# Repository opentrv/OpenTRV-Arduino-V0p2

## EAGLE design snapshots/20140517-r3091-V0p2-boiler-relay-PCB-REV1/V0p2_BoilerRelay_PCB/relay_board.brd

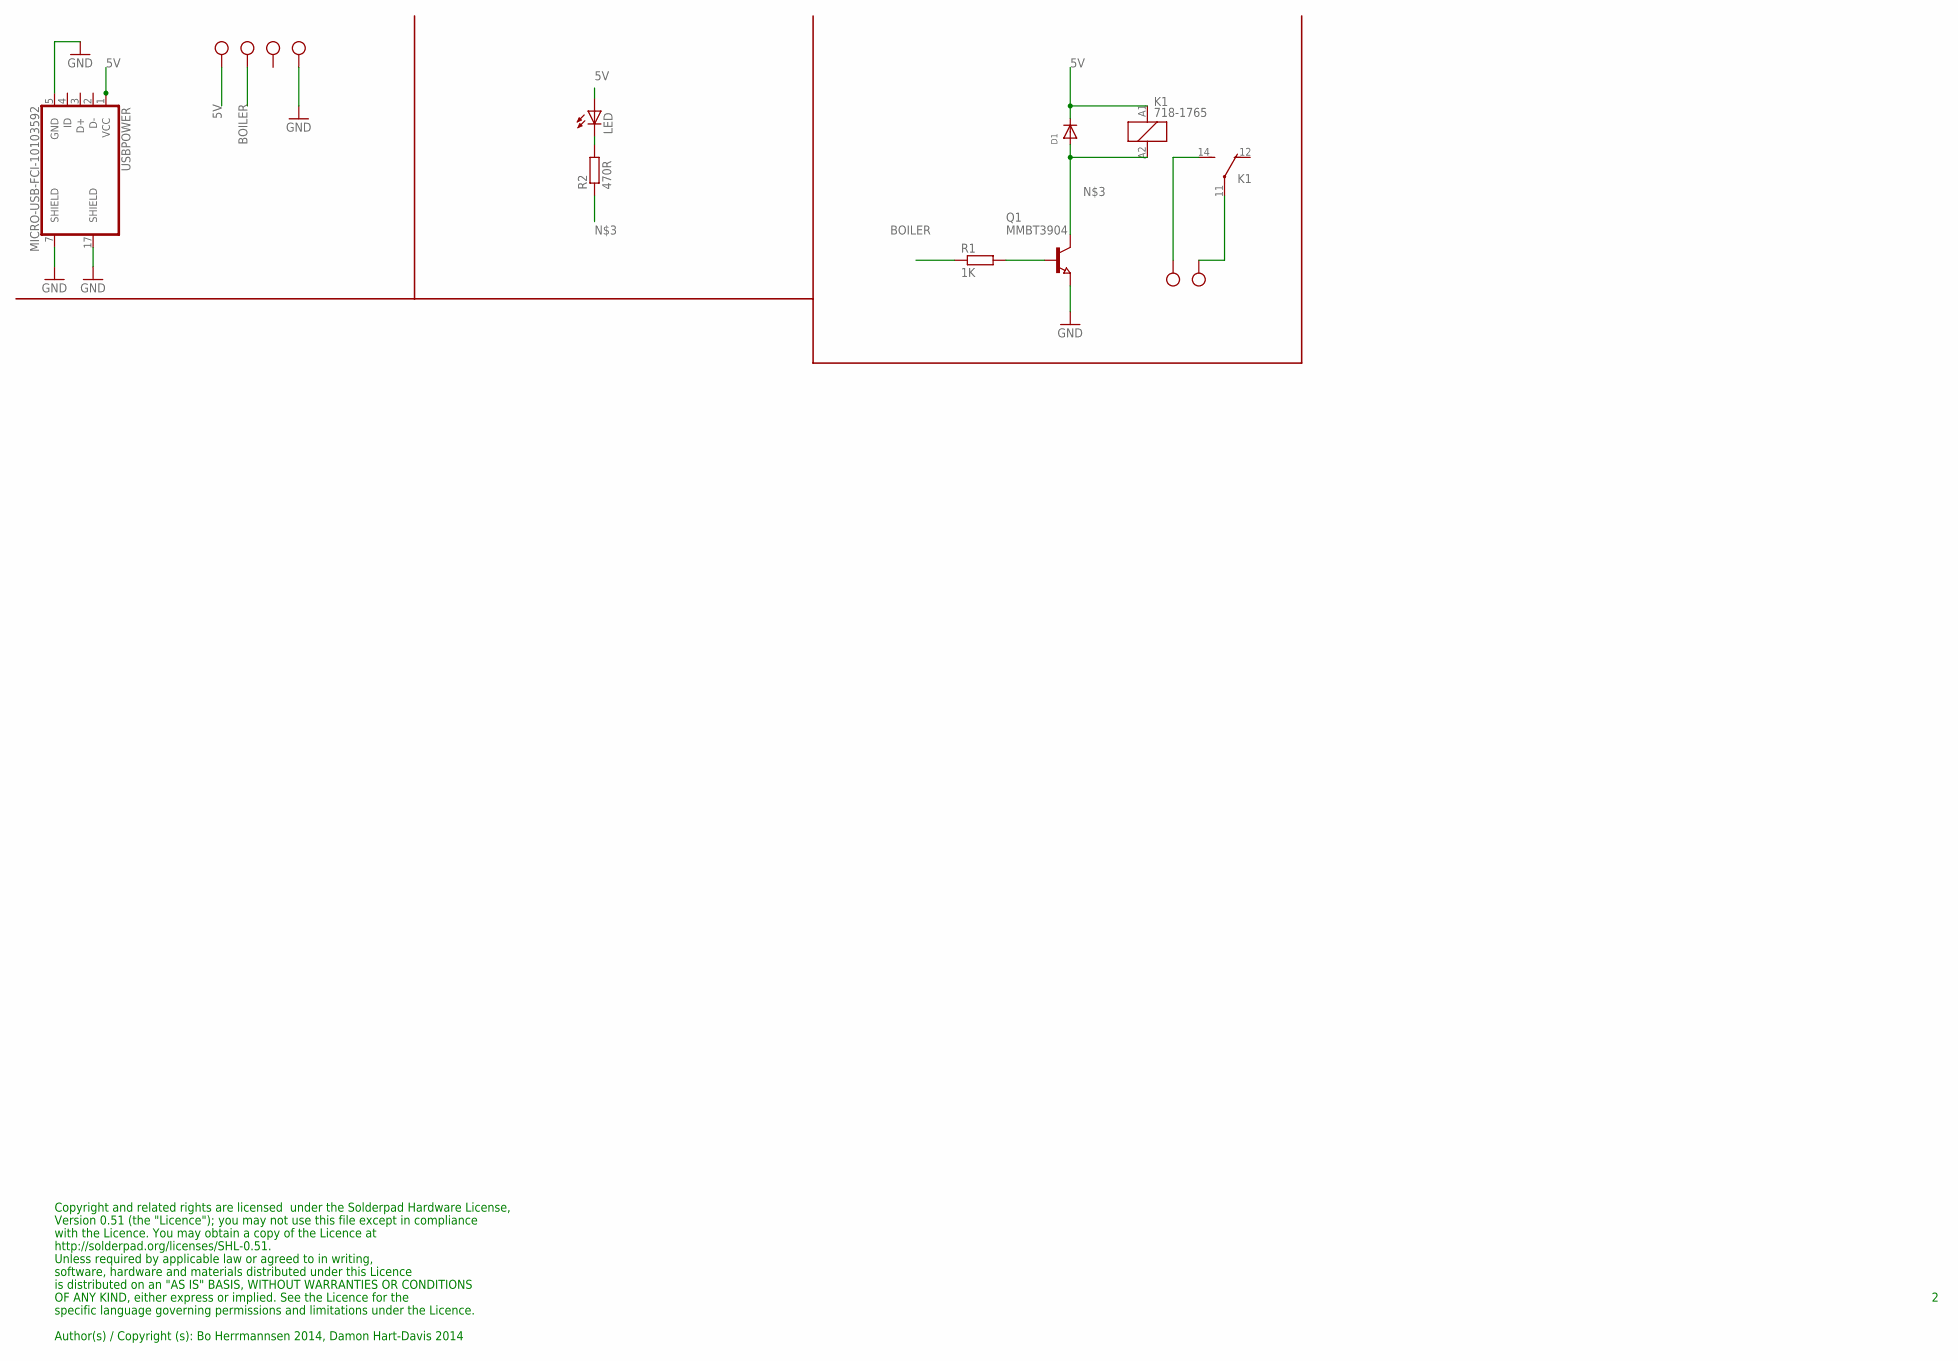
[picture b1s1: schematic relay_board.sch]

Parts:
D1: DIODESMA; SMADIODE
K1: 718-1765
LED: LED3MM
Q1: MMBT3904; SOT23
R1: 1K; R0603
R2: 470R; R0603
USBPOWER: MICRO-USB-FCI-10103592
X1, X2, X3: W237-102; SCREWTERMINAL

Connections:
5V: D1.C, K1.A1 (1), LED.A, USBPOWER.1 (VCC), X1.2
BOILER: R1.1, X1.1
GND: Q1.2 (E), USBPOWER.5 (GND), USBPOWER.7 (SHIELD), USBPOWER.17 (SHIELD), X2.2
unnamed: K1.14 (S), X3.1
unnamed: D1.A, K1.A2 (2), Q1.3 (C), R2.1
unnamed: K1.11, X3.2
unnamed: Q1.1 (B), R1.2
unnamed: LED.K (C), R2.2

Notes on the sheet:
Copyright and related rights are licensed under the Solderpad Hardware License,
Version 0.51 (the "Licence"); you may not use this file except in compliance
with the Licence. You may obtain a copy of the Licence at
http://solderpad.org/licenses/SHL-0.51.
Unless required by applicable law or agreed to in writing,
software, hardware and materials distributed under this Licence
is distributed on an "AS IS" BASIS, WITHOUT WARRANTIES OR CONDITIONS
Author(s) / Copyright (s): Bo Herrmannsen 2014, Damon Hart-Davis 2014
OF ANY KIND, either express or implied. See the Licence for the
specific language governing permissions and limitations under the Licence.

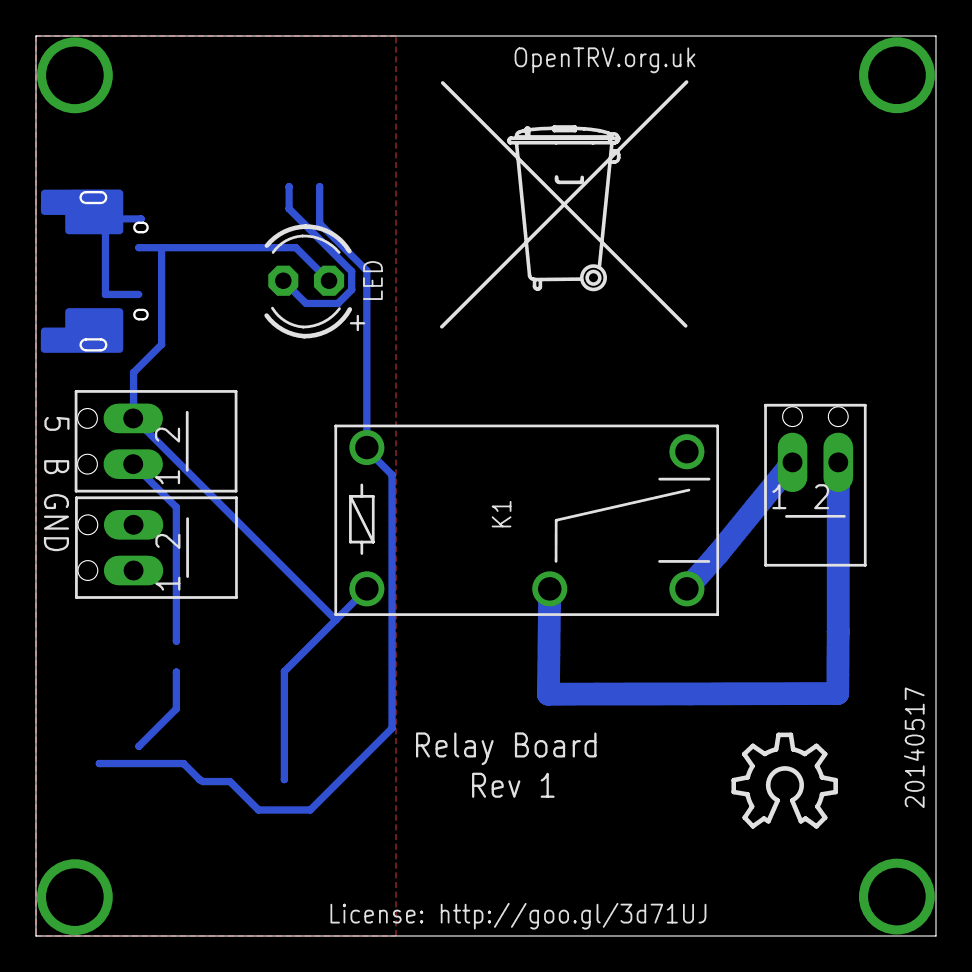
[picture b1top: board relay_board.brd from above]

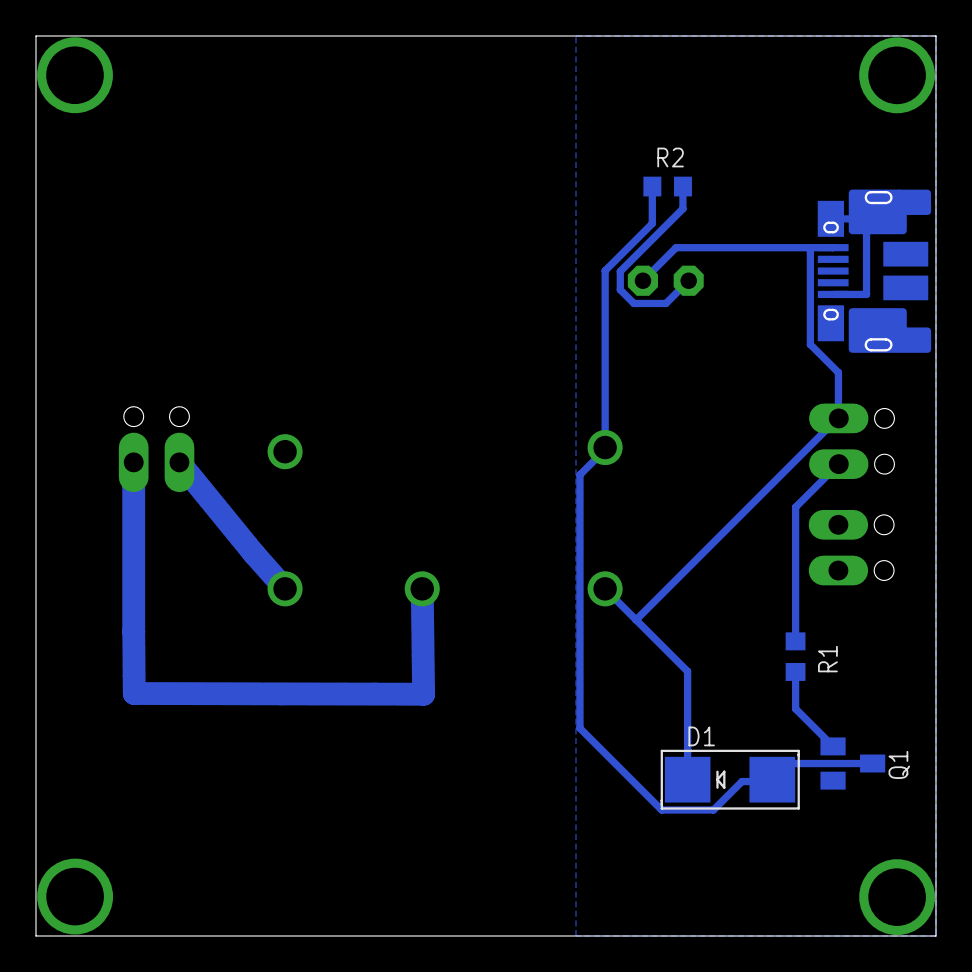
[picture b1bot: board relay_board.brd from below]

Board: 2 copper layers, 50.0 x 50.0 mm, 12 parts (5 on the bottom side), 8 nets.

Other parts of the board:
U$1: OSHW_10X200_NOTEXT
U$2: TONNE

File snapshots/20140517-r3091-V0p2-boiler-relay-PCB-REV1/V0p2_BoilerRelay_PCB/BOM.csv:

# of boards ttl,,,,5,PURPLE MEANS OK,,,
,,,,,,,,
,,,,,,,,
Quantity per board,Need to order,Seller Stock No,Manufacturer,Manufacturer Part. No.,Description,Legend,Supplier,Direct Link
1,5,714-2334,FCI,10103592-0001LF,Micro USB socket,USBPOWER,RS Components,http://uk.rs-online.com/web/p/micro-usb-connectors/7142334/
2,10, 220-4260,Phoenix Contact,MPT 0.5/ 2-2.54,Screw Terminal 2-way,"X1, X2",RS Components,http://uk.rs-online.com/web/p/pcb-terminal-blocks/2204260
1,5,710-0104,TE Connectivity,282834-2,Screw Terminal 2-way,X3,RS Components,http://uk.rs-online.com/web/p/pcb-terminal-blocks/7100104/
1,5,826-515,Avago Technologies,HLMP-K150,LED RED,LED,RS Components,http://uk.rs-online.com/web/p/visible-leds/0826515
1,5,213-2222,TE Connectivity,CRG0603F470R,470ohm,R2,RS Components,http://uk.rs-online.com/web/p/surface-mount-fixed-resistors/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
1,5,739-0303,Fairchild Semiconductor,MMBT3904,Transistor NPN,Q1,RS Components,http://uk.rs-online.com/web/p/bipolar-transistors/7390303/
1,5,721-7340,Panasonic,ERJP03F1001V,1Kohm,R1,RS Components,http://uk.rs-online.com/web/p/surface-mount-fixed-resistors/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
1,5,796-9344,Taiwan Semiconductor,RS1D,Blocking Diode,D1,RS Components,http://uk.rs-online.com/web/p/rectifier-schottky-diodes/7969344/
1,5,680-3595,TE Connectivity,PE014005,5V Non latch relay,K1,RS Components,http://uk.rs-online.com/web/p/non-latching-relays/6803593/
,,,,,,,,
1,5,,,,5*5cm Prototype Board,,Itead Studio,

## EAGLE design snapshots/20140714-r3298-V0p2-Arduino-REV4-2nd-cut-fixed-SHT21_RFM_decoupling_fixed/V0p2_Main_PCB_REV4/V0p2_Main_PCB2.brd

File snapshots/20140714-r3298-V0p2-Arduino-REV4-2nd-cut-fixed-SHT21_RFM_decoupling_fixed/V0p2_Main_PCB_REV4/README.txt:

REV 4 is RFM23B and phototransistor and SHT21 temp_RH sensor.

Using ATmega pinout for Eagle from:
http://www.faludi.com/2008/10/07/arduino-avr-library-for-eagle-layout-editor/
without explicit licence but following email permission:

    From: Rob Faludi
    Date: 13 May 2013 00:34:52 GMT+01:00
    Subject: Re: A comment from Damon Hart-Davis

    Sure, go for it!

    A new submission (form: "Contact Form")
    ============================================
    Submitted on: May 12, 2013
    Via: /contact/

    --------------------------Contact Me----------------------

    Your Name:                      Damon Hart-Davis

    Message:
    May we use your Eagle ATmega package/library:

    http://www.faludi.com/2008/10/07/arduino-avr-library-for-eagle-layout-editor/

    In our Apache/Solderpad-licenced OpenTRV project please?

    Rgds

    Damon
    http://opentrv.org.uk/

Note ITEADstudio .dru and .cam files downloaded from their site AND NOT COVERED BY OUR APACHE LICENCE
though ITEADstudio would probably be happy for you to use their service like we did!

Component-ordering document: https://docs.google.com/spreadsheet/ccc?key=0Aptz2VDSxR-zdFl5eGpmRi10SF95YnpsSWdwdnZKSFE#gid=0

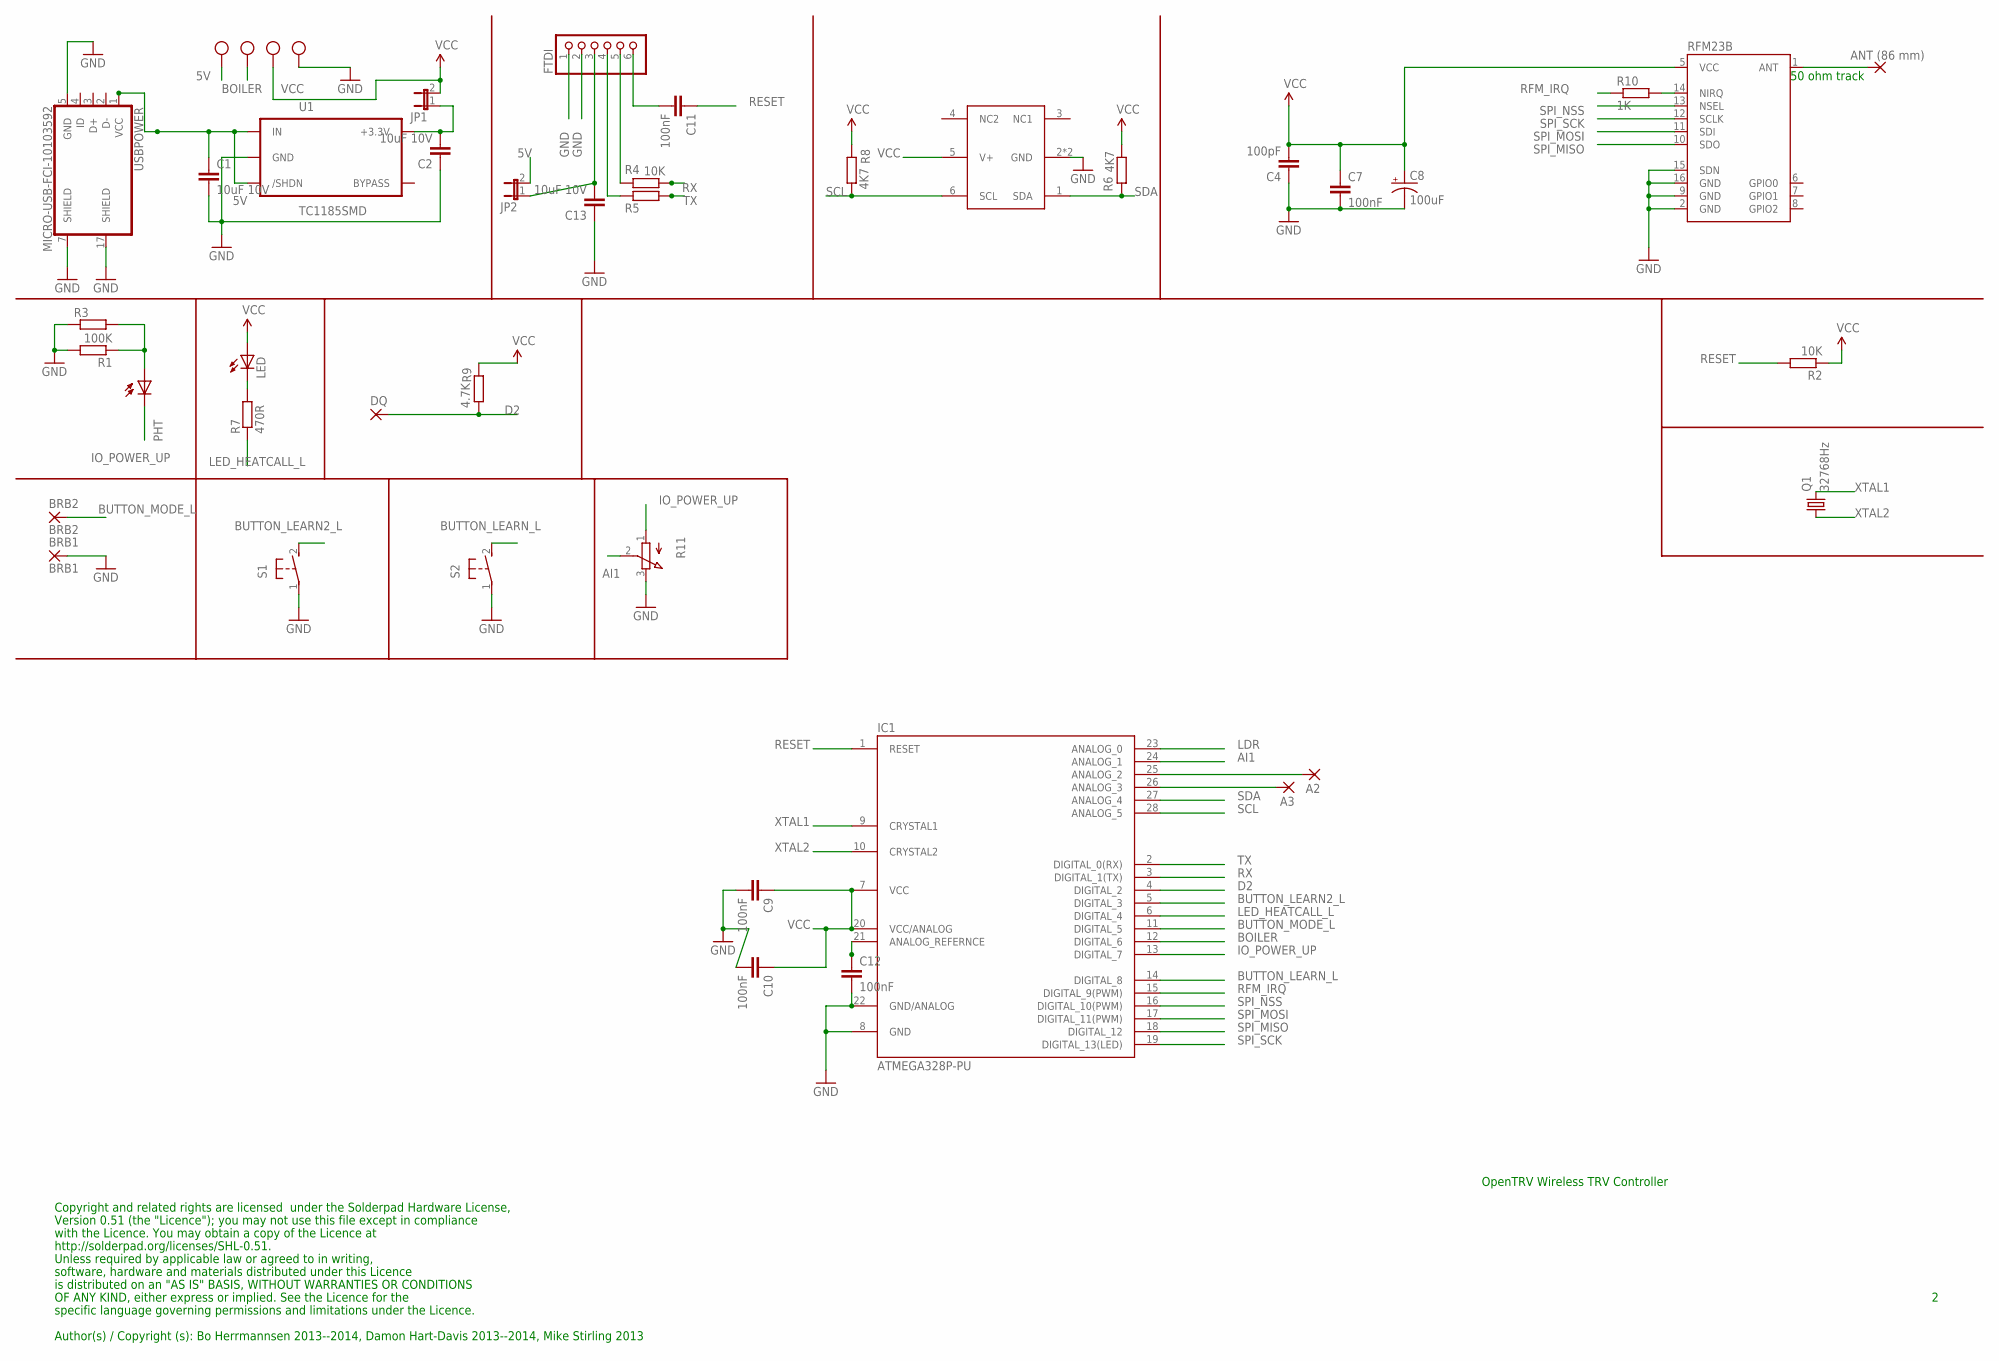
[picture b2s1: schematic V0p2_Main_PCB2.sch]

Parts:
A2, A3: 2,15/1,0
ANT1: ANT (86 mm); 2,15/1,0
BRB1: BRB1; 2,15/1,0
BRB2: BRB2; 2,15/1,0
C1, C2, C13: 10uF 10V; C0603
C4: 100pF; C0603
C7, C9, C10, C11, C12: 100nF; C0603
C8: 100uF; EIA3216
DQ: 2,15/1,0
FTDI: PINHD-1X6/90; 1X06/90
IC1: ATMEGA328P-PU; DIL28-3
JP1, JP2: JP1E; JP1
LED: LED3MM
PHT: BPX65
Q1: 32768Hz; MC-306
R1: 100K; R0603
R2, R4, R5: 10K; R0603
R3: R-EU_0309/V; 0309V
R6, R8: 4K7; R0603
R7: 470R; R0603
R9: 4.7K; R0603
R10: 1K; R0603
R11: EVUE2A; EVUE
RFM23B: RFM23B; RFM23-XXX-S1
S1, S2: 31-XX; B3F-31XX
U1: TC1185SMD; TC1185
U$4: SHT21
USBPOWER: MICRO-USB-FCI-10103592
X1, X2: W237-102; SCREWTERMINAL

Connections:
5V: C1.1, JP2.2, U1.1 (IN), U1.3 (/SHDN), USBPOWER.1 (VCC), X1.2
AI1: IC1.24 (ANALOG_1), R11.2 (S)
BOILER: IC1.12 (DIGITAL_6), X1.1
BUTTON_LEARN2_L: IC1.5 (DIGITAL_3), S1.2 (S)
BUTTON_LEARN_L: IC1.14 (DIGITAL_8), S2.2 (S)
BUTTON_MODE_L: BRB2.1, IC1.11 (DIGITAL_5)
D2: DQ.1, IC1.4 (DIGITAL_2), R9.1
GND: BRB1.1, C1.2, C2.1, C4.1, C7.2, C8.C (-), C9.2, C10.2, C12.2, C13.1, FTDI.1, FTDI.2, IC1.8 (GND), IC1.22 (GND/ANALOG), R1.2, R3.1, R11.3 (E), RFM23B.2 (GND), RFM23B.9 (GND), RFM23B.15 (SDN), RFM23B.16 (GND), S1.1, S2.1, U1.2 (GND), U$4.2 (GND), U$4.P$1 (GND), USBPOWER.5 (GND), USBPOWER.7 (SHIELD), USBPOWER.17 (SHIELD), X2.2
IO_POWER_UP: IC1.13 (DIGITAL_7), PHT.K (C), R11.1 (A)
LDR: IC1.23 (ANALOG_0), PHT.A, R1.1, R3.2
LED_HEATCALL_L: IC1.6 (DIGITAL_4), R7.1
unnamed: C11.2, FTDI.6
unnamed: FTDI.4, R5.2
unnamed: FTDI.5, R4.2
unnamed: C12.1, IC1.21 (ANALOG_REFERNCE)
unnamed: R10.2, RFM23B.14 (NIRQ)
unnamed: C2.2, JP1.1, U1.5 (+3.3V)
unnamed: C13.2, FTDI.3, JP2.1
unnamed: LED.K (C), R7.2
unnamed: A2.1, IC1.25 (ANALOG_2)
unnamed: A3.1, IC1.26 (ANALOG_3)
unnamed: ANT1.1, RFM23B.1 (ANT)
RESET: C11.1, IC1.1 (RESET), R2.2
RFM_IRQ: IC1.15 (DIGITAL_9(PWM)), R10.1
RX: IC1.3 (DIGITAL_1(TX)), R4.1
SCL: IC1.28 (ANALOG_5), R8.1, U$4.6 (SCL)
SDA: IC1.27 (ANALOG_4), R6.2, U$4.1 (SDA)
SPI_MISO: IC1.18 (DIGITAL_12), RFM23B.10 (SDO)
SPI_MOSI: IC1.17 (DIGITAL_11(PWM)), RFM23B.11 (SDI)
SPI_NSS: IC1.16 (DIGITAL_10(PWM)), RFM23B.13 (NSEL)
SPI_SCK: IC1.19 (DIGITAL_13(LED)), RFM23B.12 (SCLK)
TX: IC1.2 (DIGITAL_0(RX)), R5.1
VCC: C4.2, C7.1, C8.A (+), C9.1, C10.1, IC1.7 (VCC), IC1.20 (VCC/ANALOG), JP1.2, LED.A, R2.1, R6.1, R8.2, R9.2, RFM23B.5 (VCC), U$4.5 (V+), X2.1
XTAL1: IC1.9 (CRYSTAL1), Q1.4 (2)
XTAL2: IC1.10 (CRYSTAL2), Q1.1

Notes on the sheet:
Copyright and related rights are licensed under the Solderpad Hardware License,
Version 0.51 (the "Licence"); you may not use this file except in compliance
with the Licence. You may obtain a copy of the Licence at
http://solderpad.org/licenses/SHL-0.51.
Unless required by applicable law or agreed to in writing,
software, hardware and materials distributed under this Licence
is distributed on an "AS IS" BASIS, WITHOUT WARRANTIES OR CONDITIONS
Author(s) / Copyright (s): Bo Herrmannsen 2013--2014, Damon Hart-Davis 2013--2014, Mike Stirling 2013
OpenTRV Wireless TRV Controller
OF ANY KIND, either express or implied. See the Licence for the
specific language governing permissions and limitations under the Licence.
50 ohm track

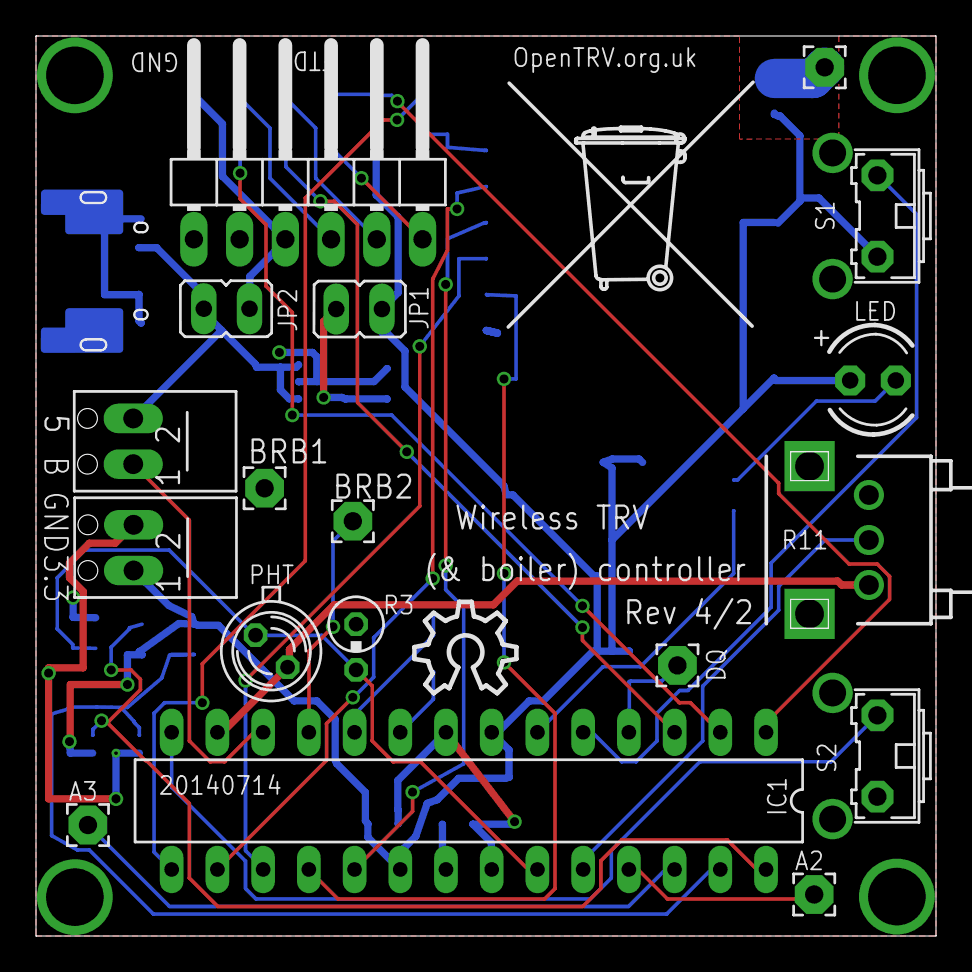
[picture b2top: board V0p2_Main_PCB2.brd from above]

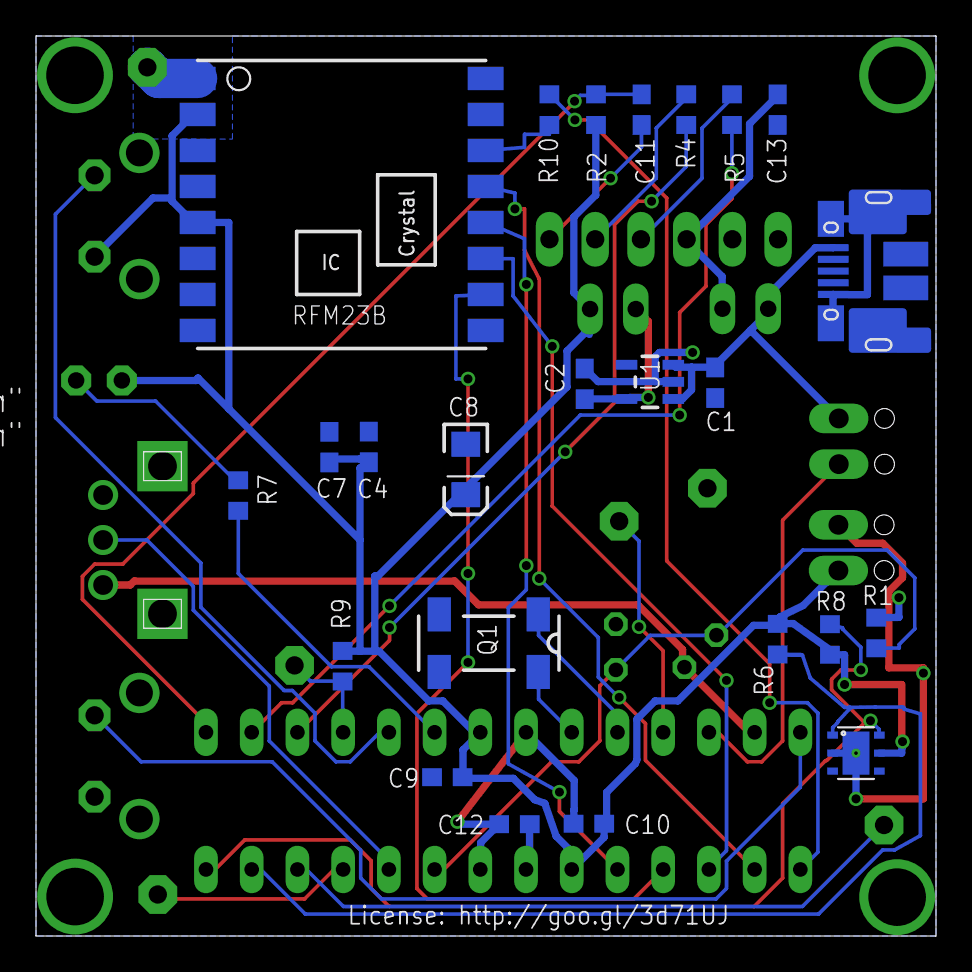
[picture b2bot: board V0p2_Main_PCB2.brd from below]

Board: 2 copper layers, 50.0 x 50.0 mm, 44 parts (24 on the bottom side), 35 nets.

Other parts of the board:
U$1: OSHW_10X200_NOTEXT
U$2: TONNE

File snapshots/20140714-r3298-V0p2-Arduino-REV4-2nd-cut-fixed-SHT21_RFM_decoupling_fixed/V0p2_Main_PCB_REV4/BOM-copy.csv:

# of boards ttl,,,,5,Green MEANS OK,,,
,,,,,,,,
,,,,,,,,
Quantity per board,Need to order,Seller Stock No,Manufacturer,Manufacturer Part. No.,Description,Legend,Supplier,Direct Link
1,5,714-2334,FCI,10103592-0001LF,Micro USB socket,USBPOWER,RS Components,http://uk.rs-online.com/web/p/micro-usb-connectors/7142334/
1,5,628-3661,Microchip,TC1185-3.3VCT713,3.3V Regulator,U1,RS Components,http://uk.rs-online.com/web/p/low-dropout-voltage-regulators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
3,15,741-4434,TDK,C1608X5R0J106M080AB,10 uF,"C1, C2, C13",RS Components,http://uk.rs-online.com/web/p/ceramic-multilayer-capacitors/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
1,5, 213-2581,TE Connectivity,CRG0603F220K,220Kohm,R1,RS Components,http://uk.rs-online.com/web/p/surface-mount-fixed-resistors/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
3,15,213-2418,TE Connectivity,CRG0603F10K,10 Kohm,"R2, R4, R5",RS Components,http://uk.rs-online.com/web/p/surface-mount-fixed-resistors/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
3,15,213-2367,TE Connectivity,CRG0603F4K7,4.7Kohm,"R6, R8, R9",RS Components,http://uk.rs-online.com/web/p/surface-mount-fixed-resistors/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
1,5,213-2222,TE Connectivity,CRG0603F470R,470ohm,R7,RS Components,http://uk.rs-online.com/web/p/surface-mount-fixed-resistors/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
5,25,264-4630,Kemet,C0603C104K4RAC,100nF,"C7, C9, C10, C11, C12",RS Components,http://uk.rs-online.com/web/p/ceramic-multilayer-capacitors/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
1,5,464-6391,AVX,06035A101JAT2A,100pF,C4,RS Components,http://uk.rs-online.com/web/p/ceramic-multilayer-capacitors/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
1,5,749-2059,Murata,GRM31CR60G107ME39L,100uF,C8,RS Components,http://uk.rs-online.com/web/p/ceramic-multilayer-capacitors/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
1,5,667-6120,EPSON TOYOCOM,"MC-306, 32.768kHz, 20ppm, 6pF",Crystal,Q1,RS Components,http://uk.rs-online.com/web/p/crystal-units/6676120
2,10, 220-4260,Phoenix Contact,MPT 0.5/ 2-2.54,Screw Terminal 2-way,"X1, X2",RS Components,http://uk.rs-online.com/web/p/pcb-terminal-blocks/2204260
1,5,786-5554,Sensirion,SHT21,SHT21,SHT21,RS Components,http://uk.rs-online.com/web/p/temperature-humidity-sensors/7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
1,5,681-2537,TE Connectivity,826947-6,FTDI 90 angle header,FTDI,RS Components,http://uk.rs-online.com/web/p/pcb-headers/6812537
1,5,674-2450,ASSMANN WSW,A 28-LC/7-T,28 pin IC Socket,IC1,RS Components,http://uk.rs-online.com/web/p/dil-sockets/6742450
2,10,251-8086,RS,W81102T3825RC,Jumper pin,"JP1, JP2",RS Components,http://uk.rs-online.com/web/p/pcb-headers/2518086
2,10,680-1461,TE Connectivity,1-881545-1,Jumper cap,"[fit to JP1, JP2]",RS Components,http://uk.rs-online.com/web/p/jumpers-shunts/6801461
1,5,826-515,Avago Technologies,HLMP-K150,LED RED,LED,RS Components,http://uk.rs-online.com/web/p/visible-leds/0826515
1,5,700-0776,Vishay,TEPT4400,60° Visible Light Phototransistor,PHT,RS Components,http://uk.rs-online.com/web/p/phototransistors/7000776/
2,10,758-1991,Alps,SKHHLQA010,Learn,"S1, S2",RS Components,http://uk.rs-online.com/web/p/tactile-switches/7581991
1,5,263-3006,Alps,RK09K1110A96,Pot. Meter,R11,RS Components,http://uk.rs-online.com/web/p/potentiometers/2633006
1,5,213-2266,TE Connectivity,CRG0603F1K0,1Kohm,R10,RS Components,http://uk.rs-online.com/web/p/surface-mount-fixed-resistors/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
1,5,119-2958,Apem,1415NC RED,Mode button,Mode,RS Components,http://uk.rs-online.com/web/p/push-button-switches/1192958
1,5,712-5320,,,84mm* of insulated semi-flexible antenna wire (~0.33sqmm). *Depends on PCB track length.,ANT,,http://uk.rs-online.com/web/p/hookup-equipment-wire/7125320
1,5,696-2260,Atmel,ATMEGA328P-PU,ATmega328P-PU,IC1,RS Components,http://uk.rs-online.com/web/p/microcontrollers/6962260
1,5,RFM23-868-S1,HopeRF,RFM23-868-S1,RFM23B,RFM23,ideetron.nl,http://www.hoperf.nl/RFM23B
1,5,,,,5*5cm Prototype Board,MAIN Board,Itead Studio,
,,,,,,,,
EXPERIMENTATION:,,,,,,,,
0,0,,,,,R3,NOT FITTED,

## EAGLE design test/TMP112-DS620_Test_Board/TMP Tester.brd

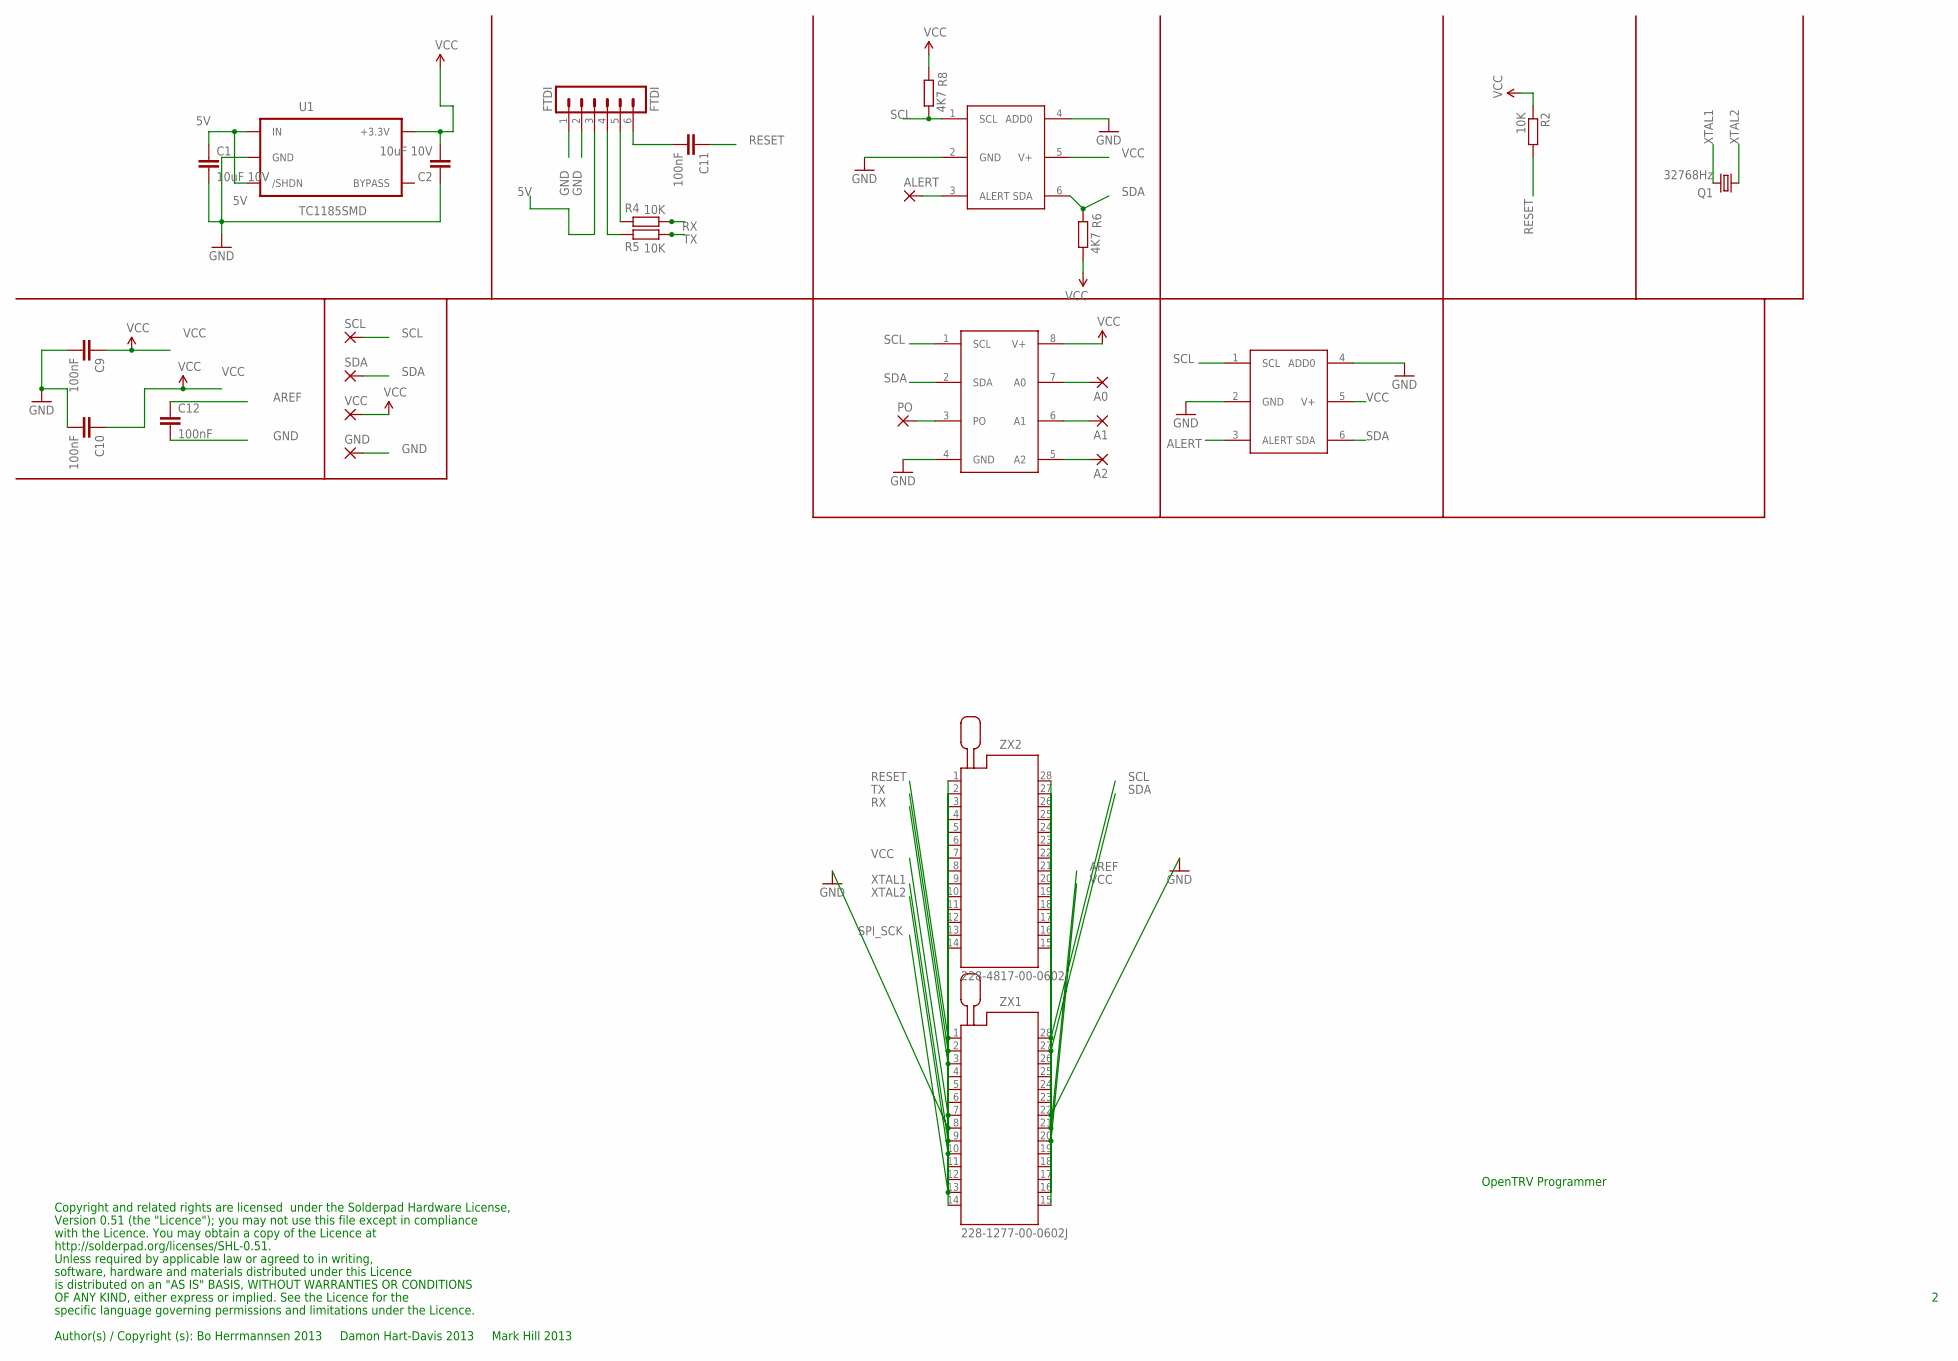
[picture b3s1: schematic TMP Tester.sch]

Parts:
A0, A1, A2: 2,15/1,0
ALERT: 2,15/1,0
C1, C2: 10uF 10V; 0603-CAP
C9, C10, C11, C12: 100nF; 0603-CAP
FTDI: FTDI; MA06-1
GND: 2,15/1,0
PO: 2,15/1,0
Q1: 32768Hz; MC-306
R2, R4, R5: 10K; R0603
R6, R8: 4K7; R0603
SCL: 2,15/1,0
SDA: 2,15/1,0
TMP112: TMP112
U1: TC1185SMD; TC1185
U$2: TMP112
U$3: DS620
VCC: 2,15/1,0
ZX1: 228-1277-00-0602J
ZX2: 228-4817-00-0602J

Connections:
5V: C1.1, FTDI.3 (VCC), U1.1 (IN), U1.3 (/SHDN)
ALERT: ALERT.1, TMP112.3 (ALERT), U$2.3 (ALERT)
AREF: C12.1, ZX1.21, ZX2.21
GND: C1.2, C2.1, C9.2, C10.2, C12.2, FTDI.1 (GND), FTDI.2 (CTS), GND.1, TMP112.2 (GND), TMP112.4 (ADD0), U1.2 (GND), U$2.2 (GND), U$2.4 (ADD0), U$3.4 (GND), ZX1.8, ZX1.22, ZX2.8, ZX2.22
unnamed: C11.2, FTDI.6 (RTS)
unnamed: FTDI.4 (TX), R5.2
unnamed: FTDI.5 (RX), R4.2
unnamed: A0.1, U$3.7 (A0)
unnamed: ZX1.4, ZX2.4
unnamed: ZX1.5, ZX2.5
unnamed: ZX1.6, ZX2.6
unnamed: A1.1, U$3.6 (A1)
unnamed: A2.1, U$3.5 (A2)
unnamed: PO.1, U$3.3 (PO)
unnamed: ZX1.11, ZX2.11
unnamed: ZX1.12, ZX2.12
unnamed: ZX1.14, ZX2.14
unnamed: ZX1.15, ZX2.15
unnamed: ZX1.16, ZX2.16
unnamed: ZX1.17, ZX2.17
unnamed: ZX1.18, ZX2.18
unnamed: ZX1.19, ZX2.19
unnamed: ZX1.23, ZX2.23
unnamed: ZX1.24, ZX2.24
unnamed: ZX1.25, ZX2.25
unnamed: ZX1.26, ZX2.26
RESET: C11.1, R2.2, ZX1.1, ZX2.1
RX: R4.1, ZX1.3, ZX2.3
SCL: R8.1, SCL.1, TMP112.1 (SCL), U$2.1 (SCL), U$3.1 (SCL), ZX1.28, ZX2.28
SDA: R6.2, SDA.1, TMP112.6 (SDA), U$2.6 (SDA), U$3.2 (SDA), ZX1.27, ZX2.27
SPI_SCK: ZX1.13, ZX2.13
TX: R5.1, ZX1.2, ZX2.2
VCC: C2.2, C9.1, C10.1, R2.1, R6.1, R8.2, TMP112.5 (V+), U1.5 (+3.3V), U$2.5 (V+), U$3.8 (V+), VCC.1, ZX1.7, ZX1.20, ZX2.7, ZX2.20
XTAL1: Q1.4 (2), ZX1.9, ZX2.9
XTAL2: Q1.1, ZX1.10, ZX2.10

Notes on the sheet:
Copyright and related rights are licensed under the Solderpad Hardware License,
Version 0.51 (the "Licence"); you may not use this file except in compliance
with the Licence. You may obtain a copy of the Licence at
http://solderpad.org/licenses/SHL-0.51.
Unless required by applicable law or agreed to in writing,
software, hardware and materials distributed under this Licence
is distributed on an "AS IS" BASIS, WITHOUT WARRANTIES OR CONDITIONS
Author(s) / Copyright (s): Bo Herrmannsen 2013 Damon Hart-Davis 2013 Mark Hill 2013
OpenTRV Programmer
OF ANY KIND, either express or implied. See the Licence for the
specific language governing permissions and limitations under the Licence.

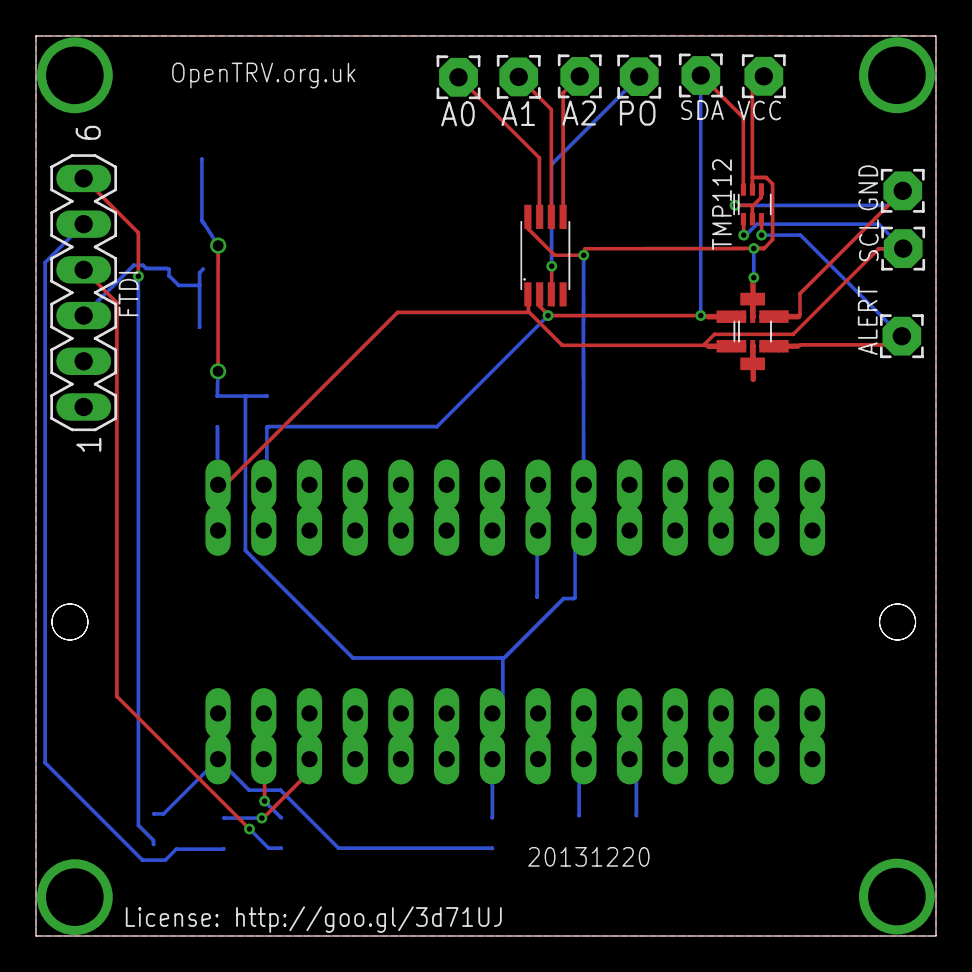
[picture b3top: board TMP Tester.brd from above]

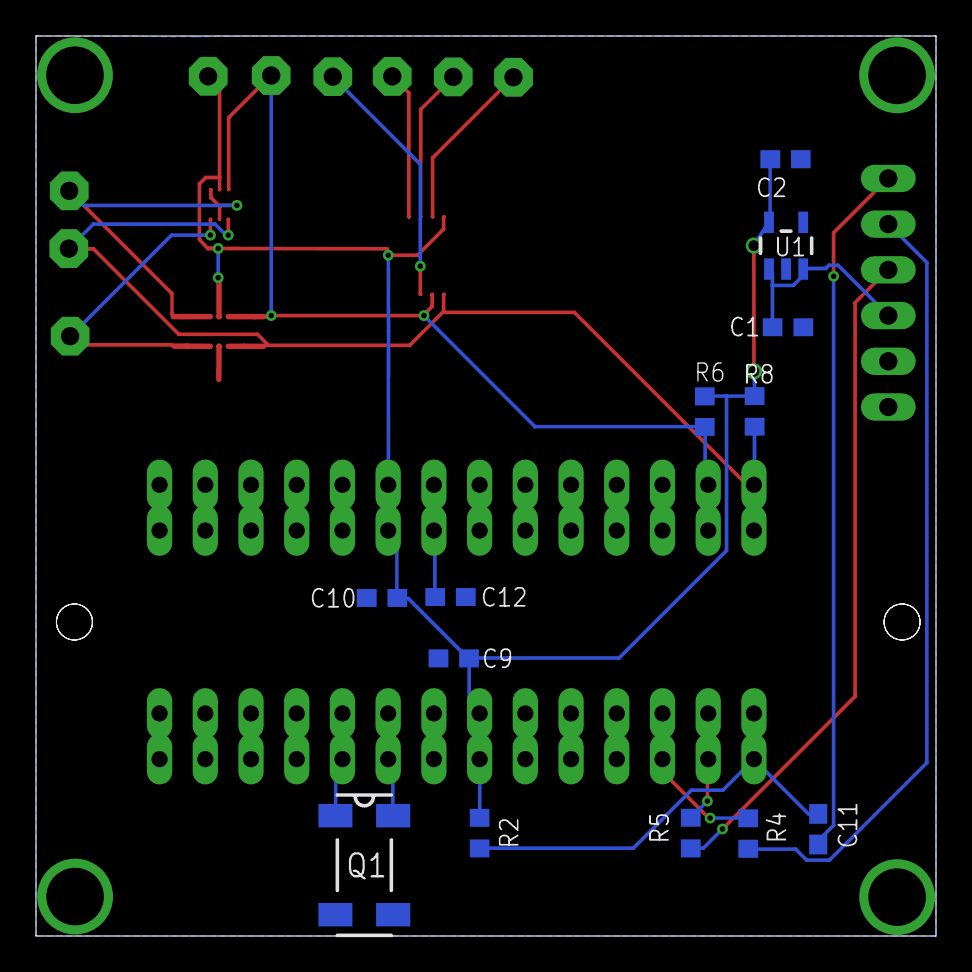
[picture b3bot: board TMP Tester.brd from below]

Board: 2 copper layers, 50.0 x 50.0 mm, 28 parts (13 on the bottom side), 35 nets.

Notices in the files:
snapshots/20140517-r3091-V0p2-boiler-relay-PCB-REV1/V0p2_BoilerRelay_PCB/relay_board.brd:
License: http://goo.gl/3d71UJ
parts and their libraries:
SparkFun-Aesthetics: Licensing: CC v3.0 Share-Alike You are welcome to use this library for commercial purposes.
